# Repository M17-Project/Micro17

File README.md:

[![CC BY-NC-SA 4.0][cc-by-nc-sa-shield]][cc-by-nc-sa]

# Micro17
M17 baseband processor board - OpenRTX on a Module.

## What is this?
Micro17 is an integrated implementation of Module17. Its PCB design is radio-dependent, but the general schematic is quite close to Module17. 
For more info about M17 and Module17, please checkout [M17's Website](https://m17project.org/) and [Module17's Github](https://github.com/M17-Project/Module_17) .

## Supported radios - variants
|Brand/Models|Status|
|-----------------|-------|
|[Generic (for all radios, can be used with modwires)](/generic/)|Hardware design WIP|
|[ICOM IC-F3XXX/4XXX/5XXX/6XXX](/icom_ICF3_4_5_6XXX/)|PoC OK, hardware design finished, fw WIP|
|[Motorola Waris (GM340/360/etc.)](/moto_waris/)|PoC OK, hardware design WIP|

## Adding support for other models
Do you have a radio that could be compatible with such an implementation? 
Any header (or ribbon cable connector) inside with the following pins can be used:
 - Flat audio in/out
 - Micro/Speaker lines
 - PTT in/out
 - Power supply 
 - (nice to have) command lines for interfacing with the radio's CPU
 
Very often, commercial radios with a scrambling board option have such lines inside. A Module17 modem is a perfect base to test a Proof of Concept before starting hardware design.
When creating a new variant of Micro17, you can use the "generic" variant as a working base, just copy and rename that folder.

## License
This work is licensed under a
[Creative Commons Attribution-NonCommercial-ShareAlike 4.0 International License][cc-by-nc-sa].

[![CC BY-NC-SA 4.0][cc-by-nc-sa-image]][cc-by-nc-sa]

[cc-by-nc-sa]: http://creativecommons.org/licenses/by-nc-sa/4.0/
[cc-by-nc-sa-image]: https://licensebuttons.net/l/by-nc-sa/4.0/88x31.png
[cc-by-nc-sa-shield]: https://img.shields.io/badge/License-CC%20BY--NC--SA%204.0-lightgrey.svg

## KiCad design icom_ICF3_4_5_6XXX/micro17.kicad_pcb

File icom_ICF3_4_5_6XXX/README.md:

# Micro17 - IC-F3/4/5/6X6X
Variant of Micro17 for ICOM IC-F commercial radios. Compatible model list is available [here](/icom_ICF3_4_5_6XXX/general_info.md).

## Flashing OpenRTX
WIP - ST-Link needed

## Installing Micro17 inside the radio
A Youtube video guide is planned soon:tm:. 
### Mobiles
Getting inside mobile IC-F5X6X/6X6X is quite straightforward: four screws will allow you to pop the bottom cover off. 
You'll need to cut/solder the following bridges:
* Cut "K", "A", "B" and "C"
* Solder/bridge "L"

You can then install Micro17 in the J1 slot. 

### Handsets
Opening a handset is a bit trickier. You'll need to remove the two knobs, unscrew the antenna nut (either using thin needle-nose pliers or the appropriate tool. Be careful as it might be glued, some light blasting with a heat gun might be needed) and the two bottom screws behind the battery. 
The following bridges will have to be changed: 
* Cut "CP2", "MIC", "AFOUT" and "PTT" 
* Solder/bridge  "CP3"
You can then install Micro17 in the J1 slot.

## Configuring Micro17
As this module is embedded inside the radio, configuration is pulled from the radio's "codeplug". This is still heavily WIP, but it's planned to use the internal command protocol one the details get figured out. 

## Wiring details
This variant is based on the experiments documented [here](https://wiki.m17project.org/icf5060_3060). 
The internal J1 connector breaks out all necessary pins.
| **Module17 equivalent Pins**          | **J1 connector**                                                                                                           |
|----------------------------|--------------------------------------------------------------------------------------------------------------------------------|
| GND (DB9 - pin 8)          | Pin 2, 17 or 39 - GND                                                                                                          |
| +12V/+8V (DB9 - pin 9)         | Pin 37 - VCC                                                                                                                   |
| RX (DB9 - pin 6)           | Pin 31 - DISC                                                                                                                  |
| TX (DB9 - pin 2)           | Pin 13 - SIGO                                                                                                                  |
| PTT_OUT (DB9 - pin 5)      | Pin 4 - PTTO (Add a 1K pullup to 5V - pin 38!)                                                                                 |
| AF_OUT (pot middle pin)    | Pin 30 - AFOUT                                                                                                                 |
| MIC_IN (jack's middle pin) | Pin 7 - MCIN                                                                                                                   |
| PTT_IN (jack's last pin)   | Pin 3 - PTTIN (Through a resistive divider: two 2.7k resistors in series between pins 2 and 3, wire to Module17 in the middle) |

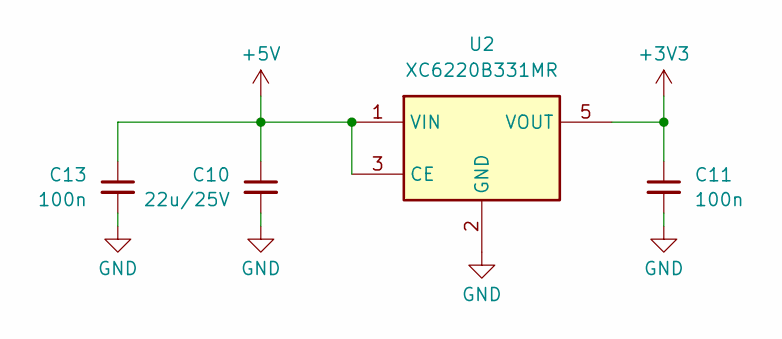
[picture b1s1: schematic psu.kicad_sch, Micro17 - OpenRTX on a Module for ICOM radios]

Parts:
C10: 22u/25V; C_0805_2012Metric; MPN C45783; LCSC C45783
C11, C13: 100n; C_0402_1005Metric; MPN C56392; LCSC C56392
U2: XC6220B331MR; SOT-23-5; MPN C3040644; LCSC C3040644

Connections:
+3V3: C11.1, U2.5 (VOUT); also elsewhere on the board
+5V: C10.1, C13.1, U2.1 (VIN), U2.3 (CE); also elsewhere on the board
GND: C10.2, C11.2, C13.2, U2.2 (GND); also elsewhere on the board

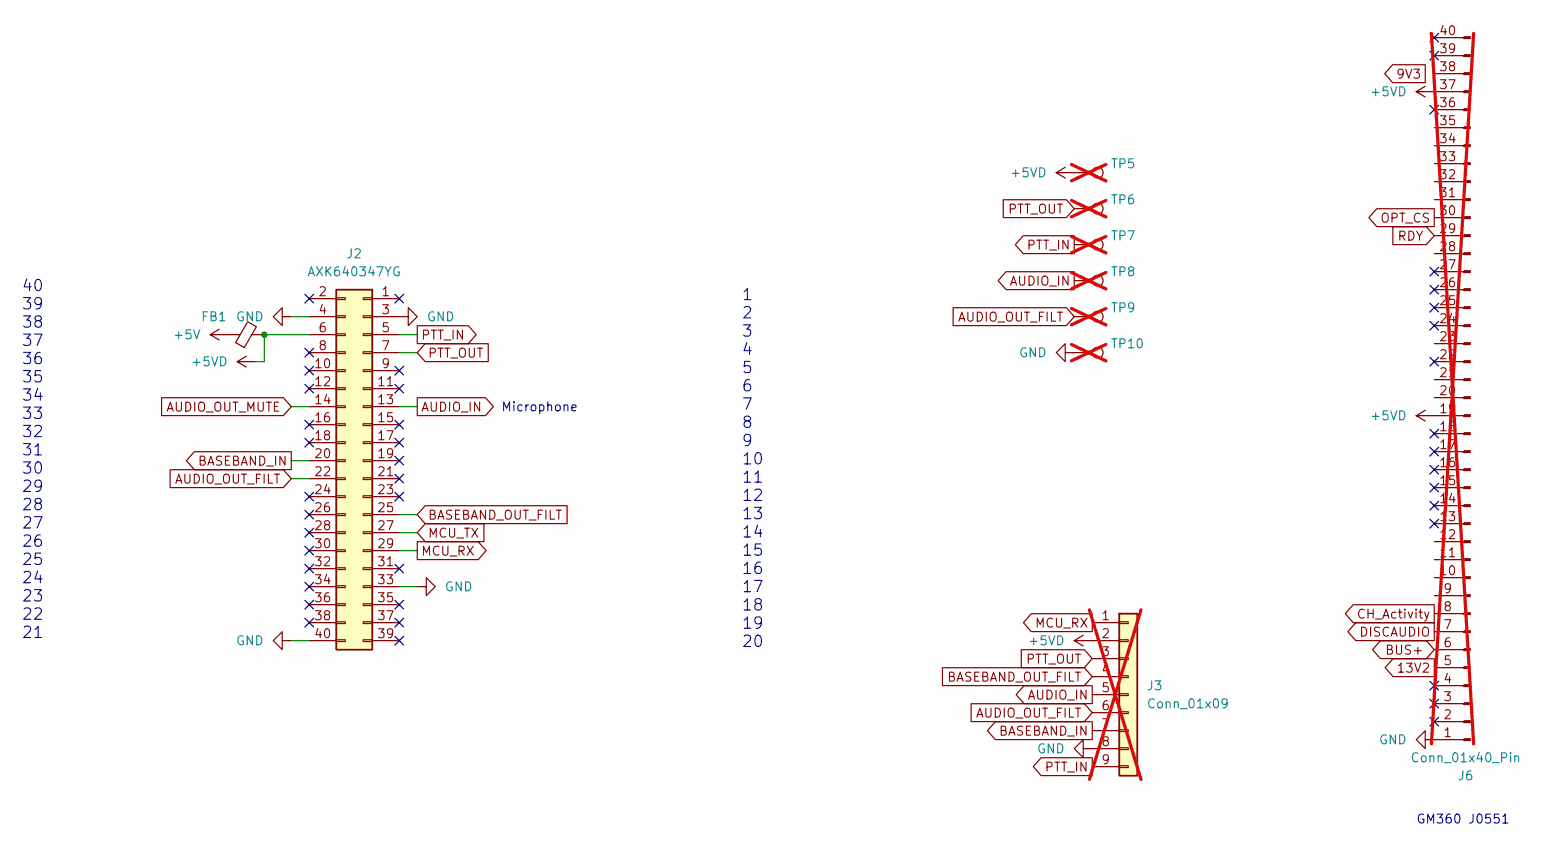
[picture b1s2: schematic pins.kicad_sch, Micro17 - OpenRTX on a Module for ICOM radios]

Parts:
FB1: FerriteBead_Small; L_0603_1608Metric_Pad1.05x0.95mm_HandSolder; MPN C2971885; LCSC C2971885
J2: AXK640347YG; MPN C2936870; LCSC C2936870
J3: Conn_01x09; PinSocket_1x09_P2.00mm_Horizontal; not fitted
J6: Conn_01x40_Pin; Hirose_FH12-40S-0.5SH_1x40-1MP_P0.50mm_Horizontal; not fitted
TP5, TP6, TP7, TP8, TP9, TP10: GP; TestPoint_Pad_D1.0mm; not fitted

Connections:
+5V: FB1.1; also elsewhere on the board
+5VD: FB1.2, J2.6, J3.2, J6.19, J6.37, TP5.1
AUDIO_IN: J2.13, J3.5, TP8.1; also elsewhere on the board
AUDIO_OUT_FILT: J2.22, J3.6, TP9.1; also elsewhere on the board
AUDIO_OUT_MUTE: J2.14; also elsewhere on the board
BASEBAND_IN: J2.20, J3.7; also elsewhere on the board
BASEBAND_OUT_FILT: J2.25, J3.4; also elsewhere on the board
GND: J2.3, J2.4, J2.33, J2.40, J3.8, J6.1, TP10.1; also elsewhere on the board
MCU_RX: J2.29, J3.1; also elsewhere on the board
MCU_TX: J2.27; also elsewhere on the board
PTT_IN: J2.5, J3.9, TP7.1; also elsewhere on the board
PTT_OUT: J2.7, J3.3, TP6.1; also elsewhere on the board

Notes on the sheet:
GM360 J0551
Microphone
40 39 38 37 36 35 34 33 32 31 30 29 28 27 26 25 24 23 22 21
1 2 3 4 5 6 7 8 9 10 11 12 13 14 15 16 17 18 19 20

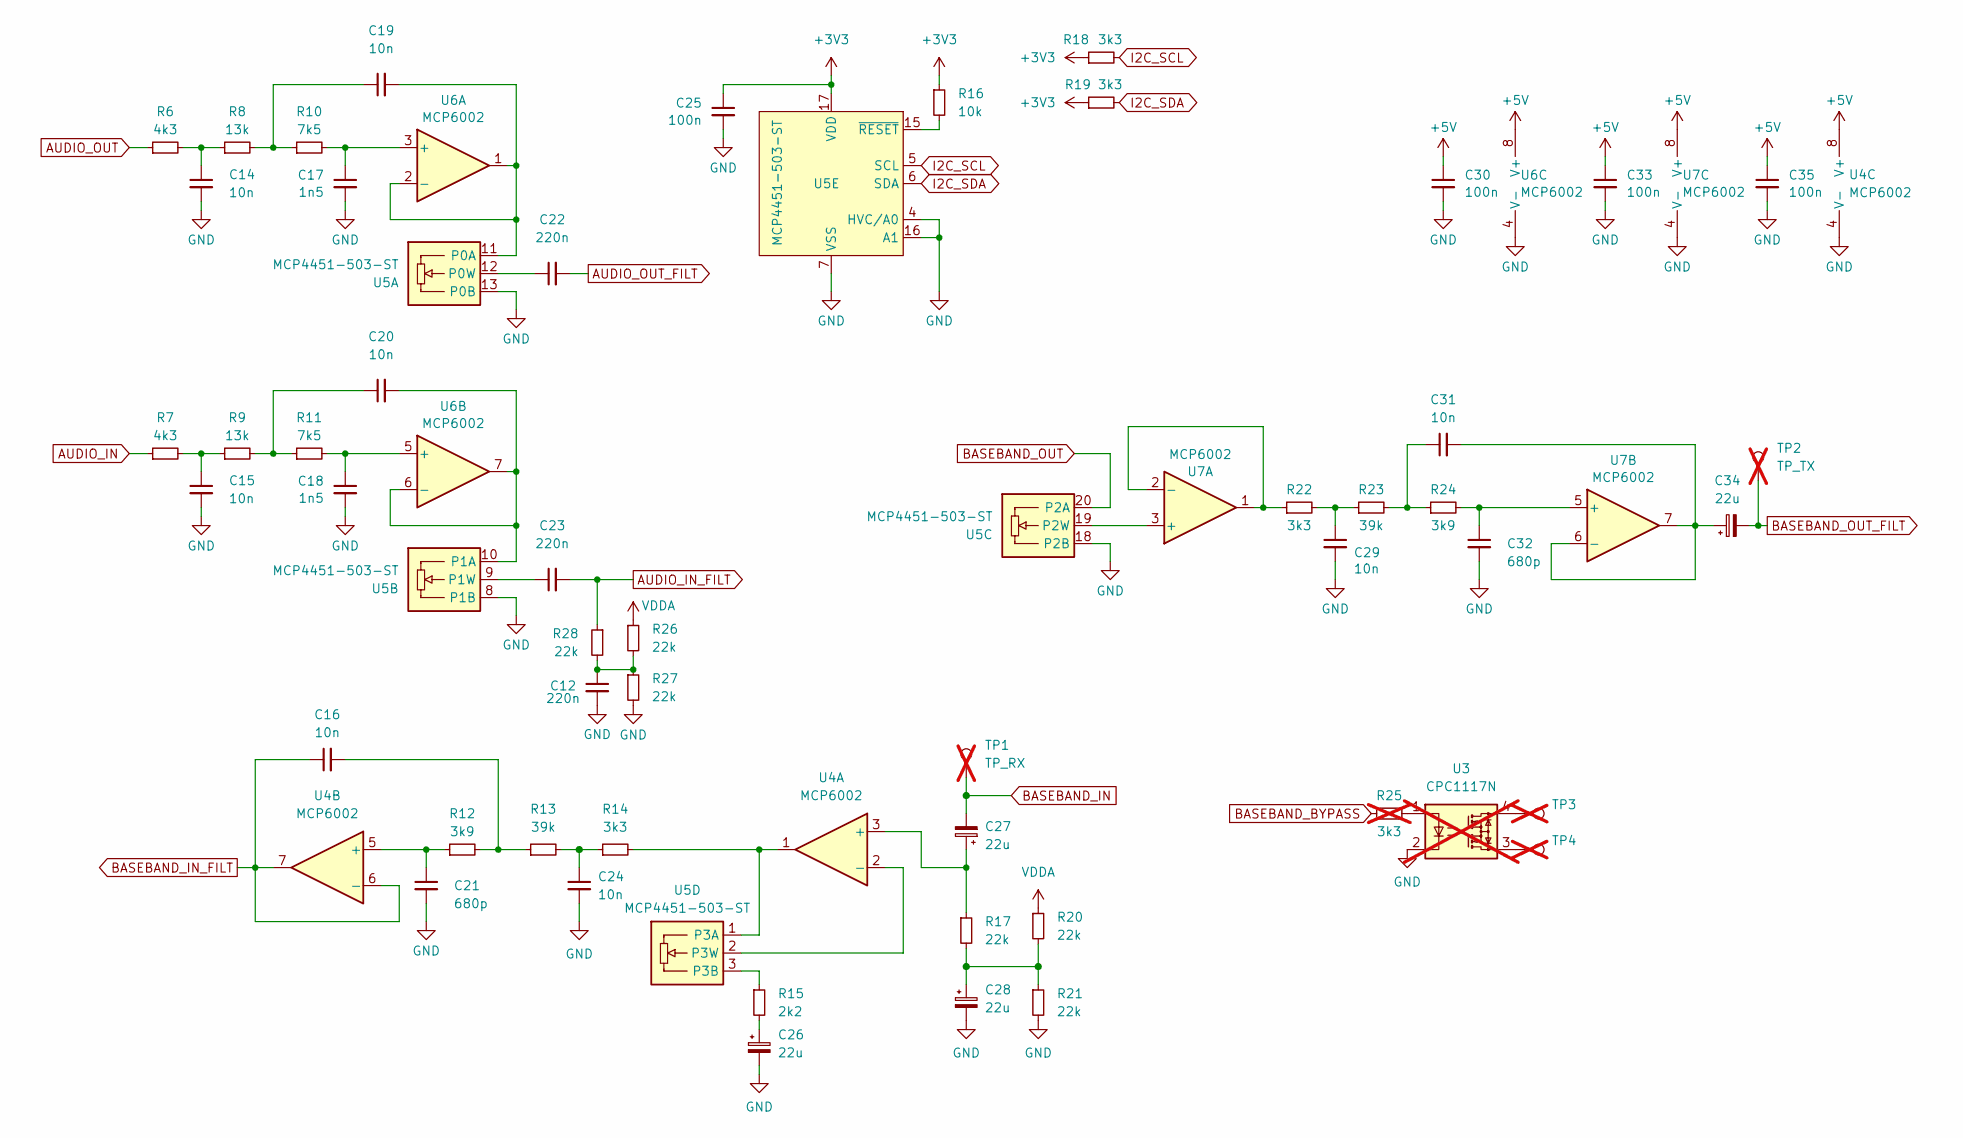
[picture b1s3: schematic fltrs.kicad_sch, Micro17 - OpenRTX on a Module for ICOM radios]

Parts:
C12, C22, C23: 220n; C_0402_1005Metric; MPN C192432; LCSC C192432
C14, C15, C16, C19, C20, C24, C29, C31: 10n; C_0402_1005Metric; MPN C60133; LCSC C60133
C17, C18: 1n5; C_0402_1005Metric; MPN C284989; LCSC C284989
C21, C32: 680p; C_0402_1005Metric; MPN C1541; LCSC C1541
C25, C30, C33, C35: 100n; C_0402_1005Metric; MPN C56392; LCSC C56392
C26, C27, C28, C34: 22u; CP_EIA-3216-18_Kemet-A; MPN C118989; LCSC C118989
R6, R7: 4k3; R_0402_1005Metric; MPN C25899; LCSC C25899
R8, R9: 13k; R_0402_1005Metric; MPN C25754; LCSC C25754
R10, R11: 7k5; R_0402_1005Metric; MPN C2960875; LCSC C2960875
R12: 3k9; R_0402_1005Metric; MPN C3015806; LCSC C3015806
R13, R23: 39k; R_0402_1005Metric; MPN C25783; LCSC C25783
R14, R18, R19, R22: 3k3; R_0402_1005Metric; MPN C25890; LCSC C25890
R15: 2k2; R_0402_1005Metric; MPN C102890; LCSC C102890
R16: 10k; R_0402_1005Metric; MPN C102749; LCSC C102749
R17, R20, R21, R26, R27, R28: 22k; R_0402_1005Metric; MPN C2909337; LCSC C2909337
R24: 3k9; R_0603_1608Metric; MPN C23018; LCSC C23018
R25: 3k3; R_0402_1005Metric; LCSC C25890; not fitted
TP1: TP_RX; TestPoint_Pad_D1.0mm; not fitted
TP2: TP_TX; TestPoint_Pad_D1.0mm; not fitted
TP3, TP4: GP; TestPoint_Pad_D1.0mm; not fitted
U3: CPC1117N; SOP-4_3.8x4.1mm_P2.54mm; not fitted
U4, U6, U7: MCP6002; DFN-8-1EP_3x2mm_P0.5mm_EP1.75x1.45mm; MPN C623660; LCSC C623660
U5: MCP4451-503-ST; TSSOP-20_4.4x6.5mm_P0.65mm; MPN C627257; LCSC C627257

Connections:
+3V3: C25.1, R16.1, R18.1, R19.1, U5.17 (VDD); also elsewhere on the board
+5V: C30.1, C33.1, C35.1, U4.8 (V+), U6.8 (V+), U7.8 (V+); also elsewhere on the board
AUDIO_IN: R7.1; also elsewhere on the board
AUDIO_IN_FILT: C23.2, R28.1; also elsewhere on the board
AUDIO_OUT: R6.1; also elsewhere on the board
AUDIO_OUT_FILT: C22.2; also elsewhere on the board
BASEBAND_BYPASS: R25.1; also elsewhere on the board
BASEBAND_IN: C27.2, TP1.1; also elsewhere on the board
BASEBAND_IN_FILT: C16.1, U4.6 (-), U4.7; also elsewhere on the board
BASEBAND_OUT: U5.20 (P2A); also elsewhere on the board
BASEBAND_OUT_FILT: C34.2, TP2.1; also elsewhere on the board
GND: C12.2, C14.2, C15.2, C17.2, C18.2, C21.2, C24.2, C25.2, C26.2, C28.2, C29.2, C30.2, C32.2, C33.2, C35.2, R21.2, R27.2, U3.2, U4.4 (V-), U4.9 (V-), U5.4 (HVC/A0), U5.7 (VSS), U5.8 (P1B), U5.13 (P0B), U5.16 (A1), U5.18 (P2B), U6.4 (V-), U6.9 (V-), U7.4 (V-), U7.9 (V-); also elsewhere on the board
I2C_SCL: R18.2, U5.5 (SCL); also elsewhere on the board
I2C_SDA: R19.2, U5.6 (SDA); also elsewhere on the board
unnamed: C12.1, R26.2, R27.1, R28.2
unnamed: C14.1, R6.2, R8.1
unnamed: C15.1, R7.2, R9.1
unnamed: C16.2, R12.2, R13.1
unnamed: C19.1, R8.2, R10.1
unnamed: C20.1, R9.2, R11.1
unnamed: C24.1, R13.2, R14.1
unnamed: C26.1, R15.2
unnamed: C28.1, R17.2, R20.2, R21.1
unnamed: C29.1, R22.2, R23.1
unnamed: C31.1, R23.2, R24.1
unnamed: R25.2, U3.1
unnamed: TP3.1, U3.4
unnamed: TP4.1, U3.3
unnamed: C27.1, R17.1, U4.3 (+)
unnamed: U4.2 (-), U5.2 (P3W)
unnamed: C21.1, R12.1, U4.5 (+)
unnamed: C19.2, U5.11 (P0A), U6.1, U6.2 (-)
unnamed: C22.1, U5.12 (P0W)
unnamed: C20.2, U5.10 (P1A), U6.6 (-), U6.7
unnamed: C23.1, U5.9 (P1W)
unnamed: U5.19 (P2W), U7.3 (+)
unnamed: R14.2, U4.1, U5.1 (P3A)
unnamed: R15.1, U5.3 (P3B)
unnamed: R16.2, U5.15 (~RESET)
unnamed: C17.1, R10.2, U6.3 (+)
unnamed: C18.1, R11.2, U6.5 (+)
unnamed: R22.1, U7.1, U7.2 (-)
unnamed: C32.1, R24.2, U7.5 (+)
unnamed: C31.2, C34.1, U7.6 (-), U7.7
VDDA: R20.1, R26.1; also elsewhere on the board

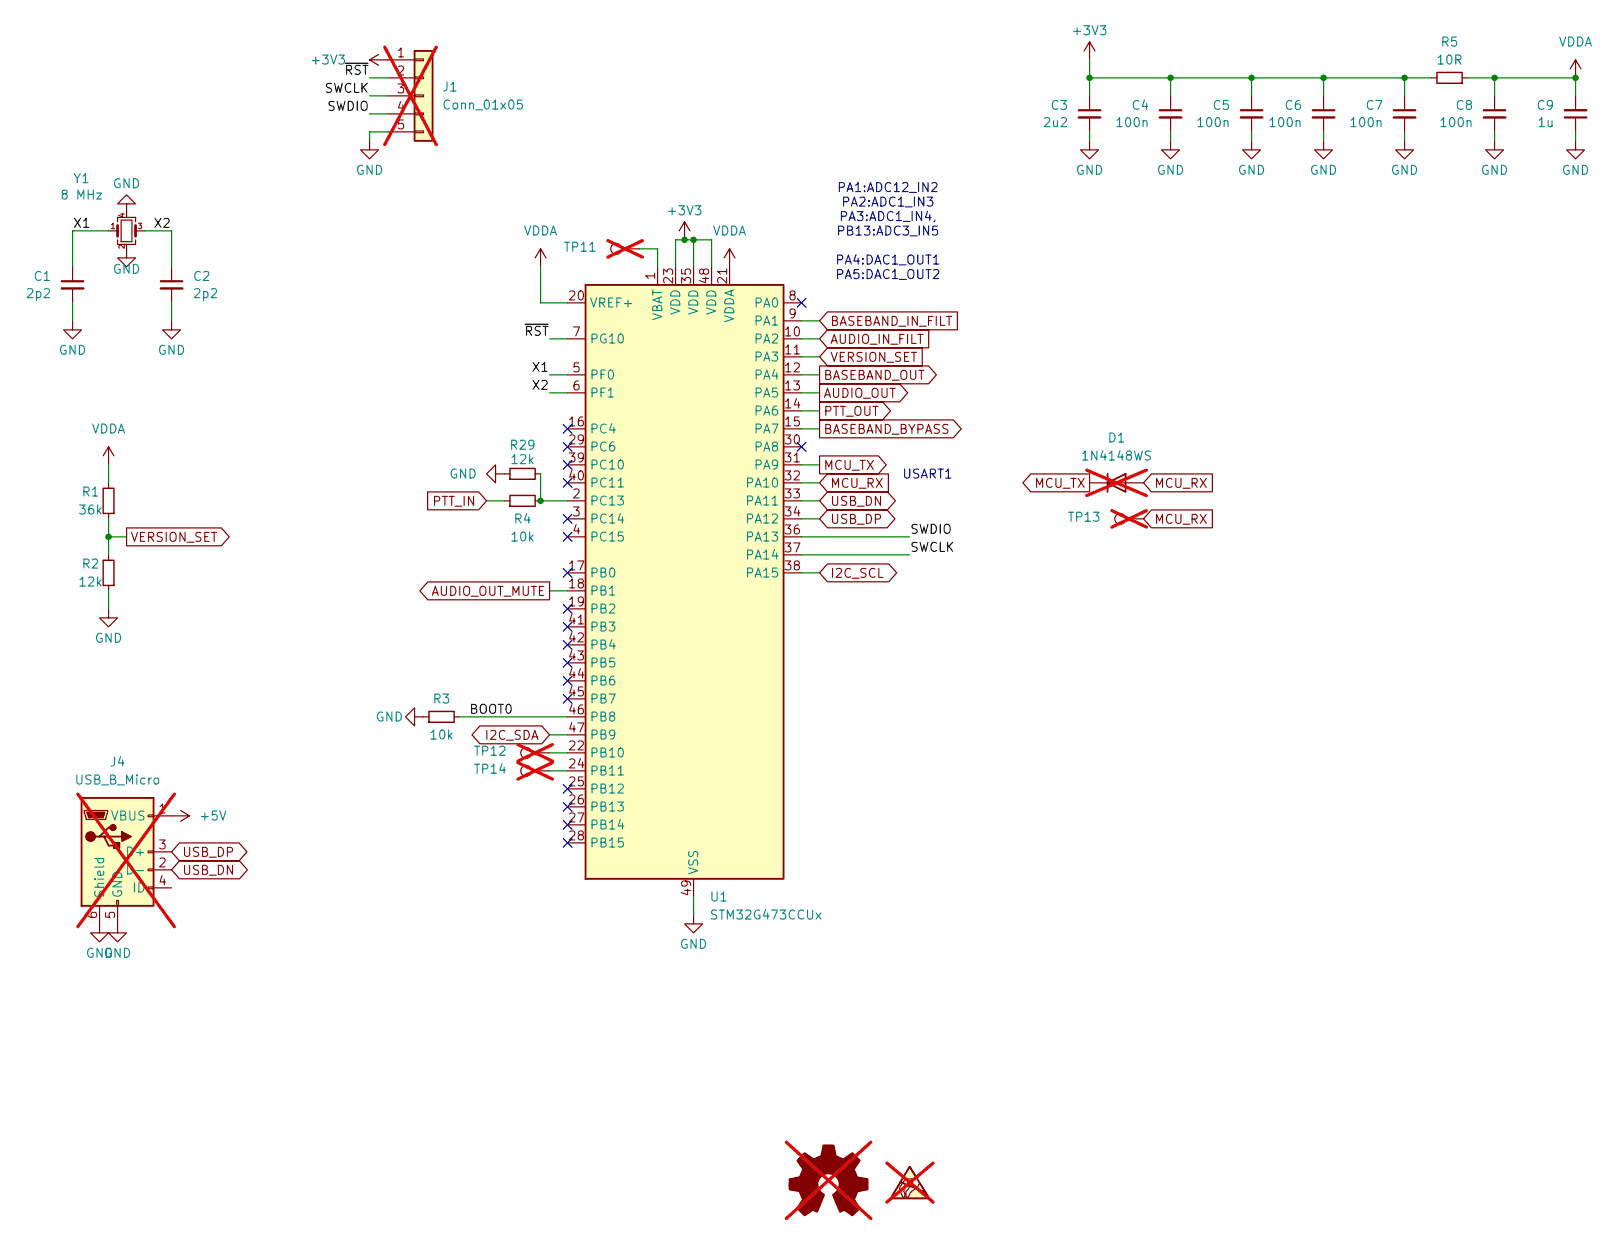
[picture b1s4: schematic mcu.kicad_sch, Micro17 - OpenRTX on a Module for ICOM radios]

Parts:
C1, C2: 2p2; C_0402_1005Metric; MPN C1559; LCSC C1559
C3: 2u2; C_0402_1005Metric; MPN C170151; LCSC C170151
C4, C5, C6, C7, C8: 100n; C_0402_1005Metric; MPN C56392; LCSC C56392
C9: 1u; C_0402_1005Metric; MPN C29266; LCSC C29266
D1: 1N4148WS; D_SOD-323; not fitted
J1: Conn_01x05; Harwin_M20-89005xx_1x05_P2.54mm_Horizontal; not fitted
J4: USB_B_Micro; USB_Micro-B_Molex_47346-0001; not fitted
R1: 36k; R_0402_1005Metric; MPN C4354982; LCSC C4354982
R2, R29: 12k; R_0402_1005Metric; MPN C25752; LCSC C25752
R3, R4: 10k; R_0402_1005Metric; MPN C102749; LCSC C102749
R5: 10R; R_0402_1005Metric; MPN C854481; LCSC C854481
SYM1: SYM_ESD_Small; ESD-Logo_6.6x6mm_SilkScreen; not fitted
SYM2: Logo_Open_Hardware_Small; OSHW-Logo_5.7x6mm_SilkScreen; not fitted
TP11, TP12, TP13, TP14: GP; TestPoint_Pad_D1.0mm; not fitted
U1: STM32G473CCUx; QFN-48-1EP_7x7mm_P0.5mm_EP5.6x5.6mm; MPN C1342773; LCSC C1342773
Y1: 8 MHz; Crystal_SMD_3225-4Pin_3.2x2.5mm; MPN C5308002; LCSC C5308002

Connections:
+3V3: C3.1, C4.1, C5.1, C6.1, C7.1, J1.1, R5.2, U1.23 (VDD), U1.35 (VDD), U1.48 (VDD); also elsewhere on the board
+5V: J4.1 (VBUS); also elsewhere on the board
/MCU/BOOT0: R3.2, U1.46 (PB8)
/MCU/SWCLK: J1.3, U1.37 (PA14)
/MCU/SWDIO: J1.4, U1.36 (PA13)
/MCU/X1: C1.1, U1.5 (PF0), Y1.1
/MCU/X2: C2.1, U1.6 (PF1), Y1.3
/MCU/~RST: J1.2, U1.7 (PG10)
AUDIO_IN_FILT: U1.10 (PA2); also elsewhere on the board
AUDIO_OUT: U1.13 (PA5); also elsewhere on the board
AUDIO_OUT_MUTE: U1.18 (PB1); also elsewhere on the board
BASEBAND_BYPASS: U1.15 (PA7); also elsewhere on the board
BASEBAND_IN_FILT: U1.9 (PA1); also elsewhere on the board
BASEBAND_OUT: U1.12 (PA4); also elsewhere on the board
GND: C1.2, C2.2, C3.2, C4.2, C5.2, C6.2, C7.2, C8.2, C9.1, J1.5, J4.5 (GND), J4.6 (Shield), R2.1, R3.1, R29.1, U1.49 (VSS), Y1.2, Y1.4; also elsewhere on the board
I2C_SCL: U1.38 (PA15); also elsewhere on the board
I2C_SDA: U1.47 (PB9); also elsewhere on the board
MCU_RX: D1.2 (A), TP13.1, U1.32 (PA10); also elsewhere on the board
MCU_TX: D1.1 (K), U1.31 (PA9); also elsewhere on the board
unnamed: TP12.1, U1.22 (PB10)
unnamed: TP14.1, U1.24 (PB11)
unnamed: R4.2, R29.2, U1.2 (PC13)
unnamed: TP11.1, U1.1 (VBAT)
PTT_IN: R4.1; also elsewhere on the board
PTT_OUT: U1.14 (PA6); also elsewhere on the board
USB_DN: J4.2 (D-), U1.33 (PA11)
USB_DP: J4.3 (D+), U1.34 (PA12)
VDDA: C8.1, C9.2, R1.2, R5.1, U1.20 (VREF+), U1.21 (VDDA); also elsewhere on the board
VERSION_SET: R1.1, R2.2, U1.11 (PA3)

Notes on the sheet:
USART1
PA1:ADC12_IN2 PA2:ADC1_IN3 PA3:ADC1_IN4, PB13:ADC3_IN5 PA4:DAC1_OUT1 PA5:DAC1_OUT2

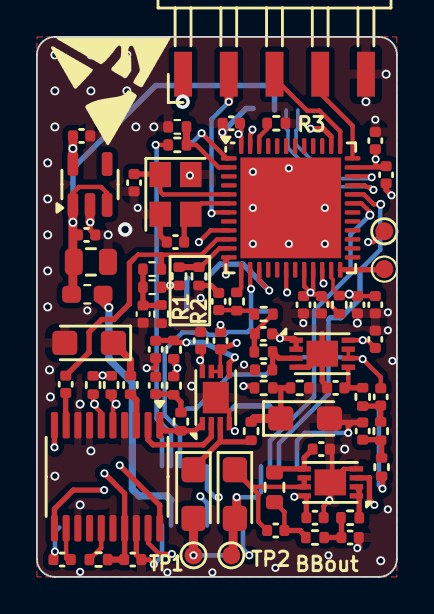
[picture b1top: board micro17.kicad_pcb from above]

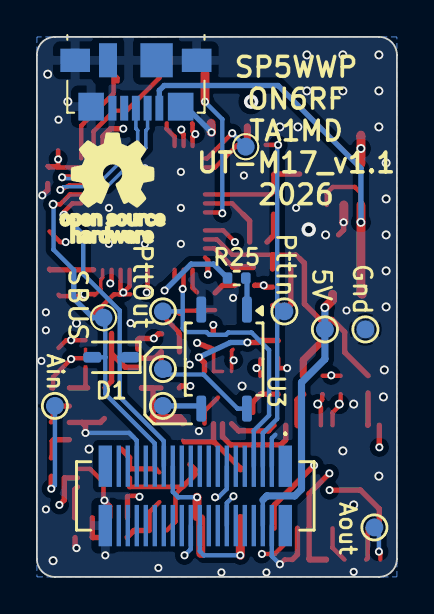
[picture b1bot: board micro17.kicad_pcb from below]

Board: 4 copper layers, 20.0 x 30.0 mm, 93 parts (16 on the bottom side), 64 nets.

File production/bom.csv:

Designator,Footprint,Quantity,Value,LCSC Part #
"C1, C2",0402,2,2p2,C1559
C10,0805,1,22u/25V,C45783
"C11, C13, C25, C30, C33, C35, C4, C5, C6, C7, C8",0402,11,100n,C56392
"C12, C22, C23",0402,3,220n,C192432
"C14, C15, C16, C19, C20, C24, C29, C31",0402,8,10n,C60133
"C17, C18",0402,2,1n5,C284989
"C21, C32",0402,2,680p,C1541
"C26, C27, C28, C34",CP_EIA-3216-18_Kemet-A,4,22u,C118989
C3,0402,1,2u2,C170151
C9,0402,1,1u,C29266
FB1,0603,1,FerriteBead_Small,C2971885
J2,AXK640347YG,1,AXK640347YG,C2936870
R1,0402,1,36k,C4354982
"R10, R11",0402,2,7k5,C2960875
R12,0402,1,3k9,C3015806
"R13, R23",0402,2,39k,C25783
"R14, R18, R19, R22",0402,4,3k3,C25890
R15,0402,1,2k2,C102890
"R16, R3, R30, R4",0402,4,10k,C102749
"R17, R20, R21, R26, R27, R28",0402,6,22k,C2909337
R2,0402,1,12k,C25752
R24,0603,1,3k9,C23018
R5,0402,1,10R,C854481
"R6, R7",0402,2,4k3,C25899
"R8, R9",0402,2,13k,C25754
U1,QFN-48-1EP_7x7mm_P0.5mm_EP5.6x5.6mm,1,STM32G473CCUx,C1342773
U2,SOT-23-5,1,XC6220B331MR,C3040644
"U4, U6, U7",DFN-8-1EP_3x2mm_P0.5mm_EP1.75x1.45mm,3,MCP6002,C623660
U5,TSSOP-20_4.4x6.5mm_P0.65mm,1,MCP4451-503-ST,C627257
Y1,Crystal_SMD_3225-4Pin_3.2x2.5mm,1,8 MHz,C5308002

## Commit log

2023-12-05 license update
2023-12-05 cleanup
2023-12-05 thanks DM4RCO!
2023-12-06 AT commands update
2023-12-17 gitignore update
2024-02-21 WIP filters
2024-02-26 First Edits
    Added J1 connector, finished filters and swapped µC to STM32G473
2024-02-29 PCB routed, gerbers and ibom included
2024-02-29 Updates
    GP relay added,
    3v3 added to programming conn.
    diode(dnp) added for motorola type internal bus.
2024-02-29 LCSC part numbers included into schematics
2024-03-02 J2 Corrected, More TP added.
2024-03-04 PA2 Bias add, USB conn add.
2024-03-04 Changed PA2 bias circuit
2024-03-04 Fixed some netlist overlaps and added a few mentions on readme.md
2024-03-04 added .pos and bom
2024-03-04 production files added.
2024-03-06 cosmetic changes to the schematic layout
    - R25 - DNP
    - PDF render update
2024-03-06 typo fix
2024-03-06 Bias voltage changed, usart rx tp add
2024-03-06 authors list fix
2024-03-06 damned authors list
2024-03-06 R30 Added
2024-04-16 Reorganized folder structure for variants
    Created one folder per variant, reworked the Readme.md for clarity.
2024-04-16 Update README.md
    closing parenthesis
2024-04-19 photo update
2024-04-19 Added general informations on ICOM radios.
2024-04-19 Rename general_info to general_info.md
2024-09-25 Update general_info.md
    Added fcc info numbers
2025-06-13 ICOM: fixed floating VREF+ pin
    KiCAD version bumped up to 9.0.2
2026-02-03 re-routed debug UART
